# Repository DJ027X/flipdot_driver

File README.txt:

######################
A word about the license
######################
In this repo, you'll find the EDA design files for my RISC-V based flipdot display driver.
In the interest of preventing an entity from profiting off of my work or its derivitives without my permission, everything in this repo is released under the Creative Commons license BY-NC-SA.
Feel free to modify and redistribute my work (with attribution to me, and under the same BY-NC-SA license), just don't use the work for profit.
Please contact me if you would like to request exemption from the terms of the license.

######################
Project progress
######################
This project is INCOMPLETE and IN-PROGRESS.
At the moment, only the schematic exists; no layout design yet.
The schematic is very near completion, and I'm currently working on finishing touches, and reviewing the design.

######################
Design details/notes
######################
This project is being designed with the open-source KiCAD toolchain. I'm tending toward openness with this project, but my design does use an FT2232D, and my license isn't truly FOSS compliant. More FOSS friendly versions may come up in the future.
My flipdot display driver is intended for use with a Luminator MAX 3000 flipdot display.
My board will mount onto the back of the flipdot display, and connect to it via a board-to-board connector (samtec part SSQ-132-01-G-Q at the moment).
Each dot on the Luminator MAX 3000 is matrixed in such a way that lends itself to be driven by what is essentially an H-bridge. (diodes in the display circuitry complicate things a tad, which is why it's not exactly an H-bridge driver, but pretty close)
My driver uses power MOSFETs arranged in an H-bridge-like topology to drive current in short (on the order of millisecond) pulses in one direction or another through the coil of each dot to flip it on (bright side visable) or off (black side visible), depending on the cirection of the current
There is 1/2 of this H-bridge-like circuit (quarter bridge?) driving each row and column on the display, effectively allowing the driver to multiplex the dots.
The quarter-bridge driver circuitry is controlled by data stored in 2 (extendable) shift registers, one for the rows and one for the columns.
Pulsing an output enable signal on the shift registers drives the selected quarter-bridge circuits (based on the output from the shift register) for the duration of the pulse.
If one wishes to extend their display with yet another (actually, an arbitrary number of) Luminator MAX 3000 board, I've added a connector that will be used (when I get around to designing the second board) to extend the shift registers to the additional board, which will house it's own section of the shift register and dedicated quarter-bridge driver circuitry.
The brain of the operation is the FE310-G000, a VERY new RISC-V based microcontroller released by SiFive.
Along with the uC are the typical auxilary chips: memory and serial to UART/JTAG to program the uC.
The Luminator MAX 3000 also has 1 LED per dot. They are all connected to the same power pins, so they're either all on, or all off.
I intend to control the brightness with PWM.
Under normal use, the board will be supplied with 12V from a power brick. From there, several buck converters will provide the voltages for the shift registers, memory, uC, etc.
There will also be a voltage negater (generating -12V), to provide a potential of 24V for the LEDs.
I'm currently working full time, so progress on this relatively large hobby project has been slow, but I'll have a physical board eventually! (Aiming for 3 months from now (12/27/2018))

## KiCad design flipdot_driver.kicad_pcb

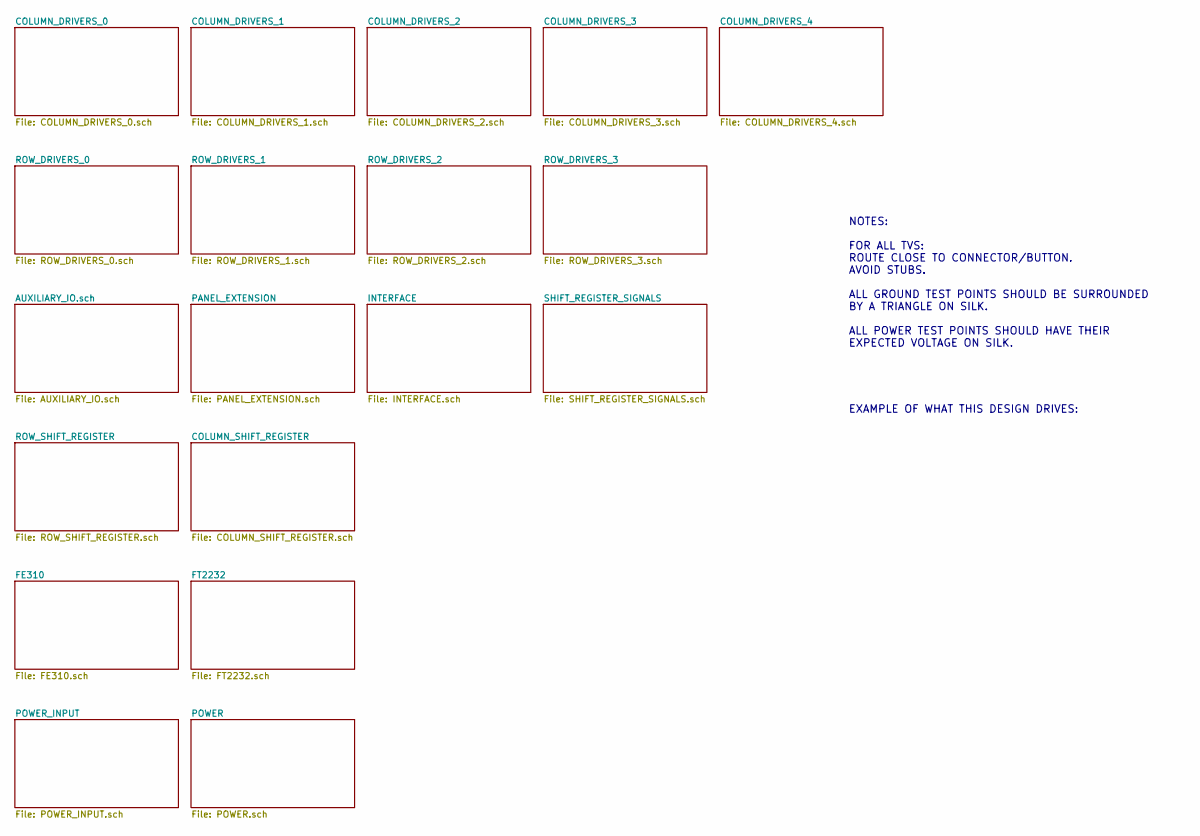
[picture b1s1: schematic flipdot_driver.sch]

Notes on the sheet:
NOTES: FOR ALL TVS: ROUTE CLOSE TO CONNECTOR/BUTTON. AVOID STUBS. ALL GROUND TEST POINTS SHOULD BE SURROUNDED BY A TRIANGLE ON SILK. ALL POWER TEST POINTS SHOULD HAVE THEIR EXPECTED VOLTAGE ON SILK.
EXAMPLE OF WHAT THIS DESIGN DRIVES:

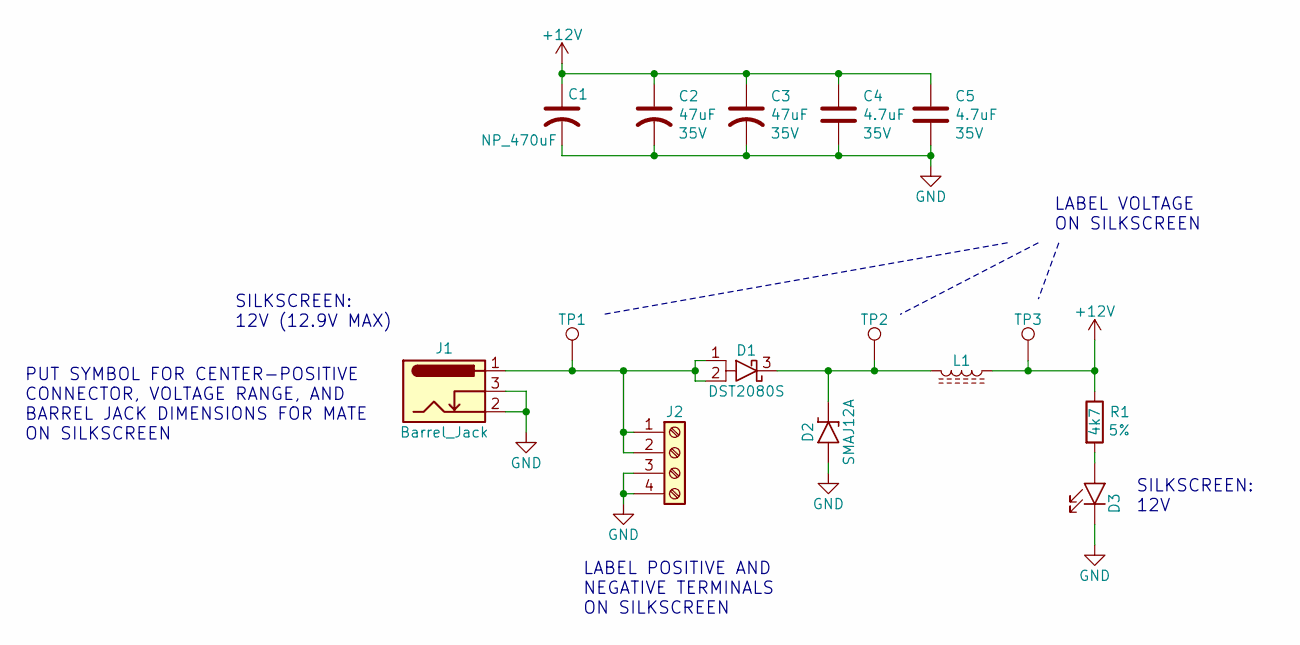
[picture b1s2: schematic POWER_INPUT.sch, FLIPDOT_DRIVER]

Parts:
C1: NP_470uF
C2, C3: ‎ESK476M035AC3AA‎; Rating 35V
C4, C5: ‎CL21A475KLCLQNC‎; C_0805_2012Metric; Rating 35V
D1: DST2080S; TO-277B
D2: SMAJ12A; D_SMA
D3: LED_GENERIC_0805; D_0805_2012Metric
J1: Barrel_Jack; BarrelJack_Wuerth_6941xx301002
J2: Screw_Terminal_01x04; TERMINAL_BLOCK_5mm_1x4
L1: BLM31SN500SZ1L; L_1206_3216Metric
R1: CRG0603F4K7; R_0603_1608Metric; TOLERANCE 5%
TP1, TP2, TP3: TestPoint; TestPoint_THTPad_D1.0mm_Drill0.5mm

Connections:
+12V: C1.1, C2.1, C3.1, C4.1, C5.1, L1.1, R1.1, TP3.1; also elsewhere on the board
GND: C1.2, C2.2, C3.2, C4.2, C5.2, D2.2 (A), D3.1 (K), J1.2, J1.3, J2.3, J2.4; also elsewhere on the board
unnamed: D1.1 (A1), D1.2 (A2), J1.1, J2.1, J2.2, TP1.1
unnamed: D1.3 (K), D2.1 (K), L1.2, TP2.1
unnamed: D3.2 (A), R1.2

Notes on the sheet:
PUT SYMBOL FOR CENTER-POSITIVE CONNECTOR, VOLTAGE RANGE, AND BARREL JACK DIMENSIONS FOR MATE ON SILKSCREEN
LABEL POSITIVE AND NEGATIVE TERMINALS ON SILKSCREEN
SILKSCREEN: 12V (12.9V MAX)
SILKSCREEN: 12V
LABEL VOLTAGE ON SILKSCREEN

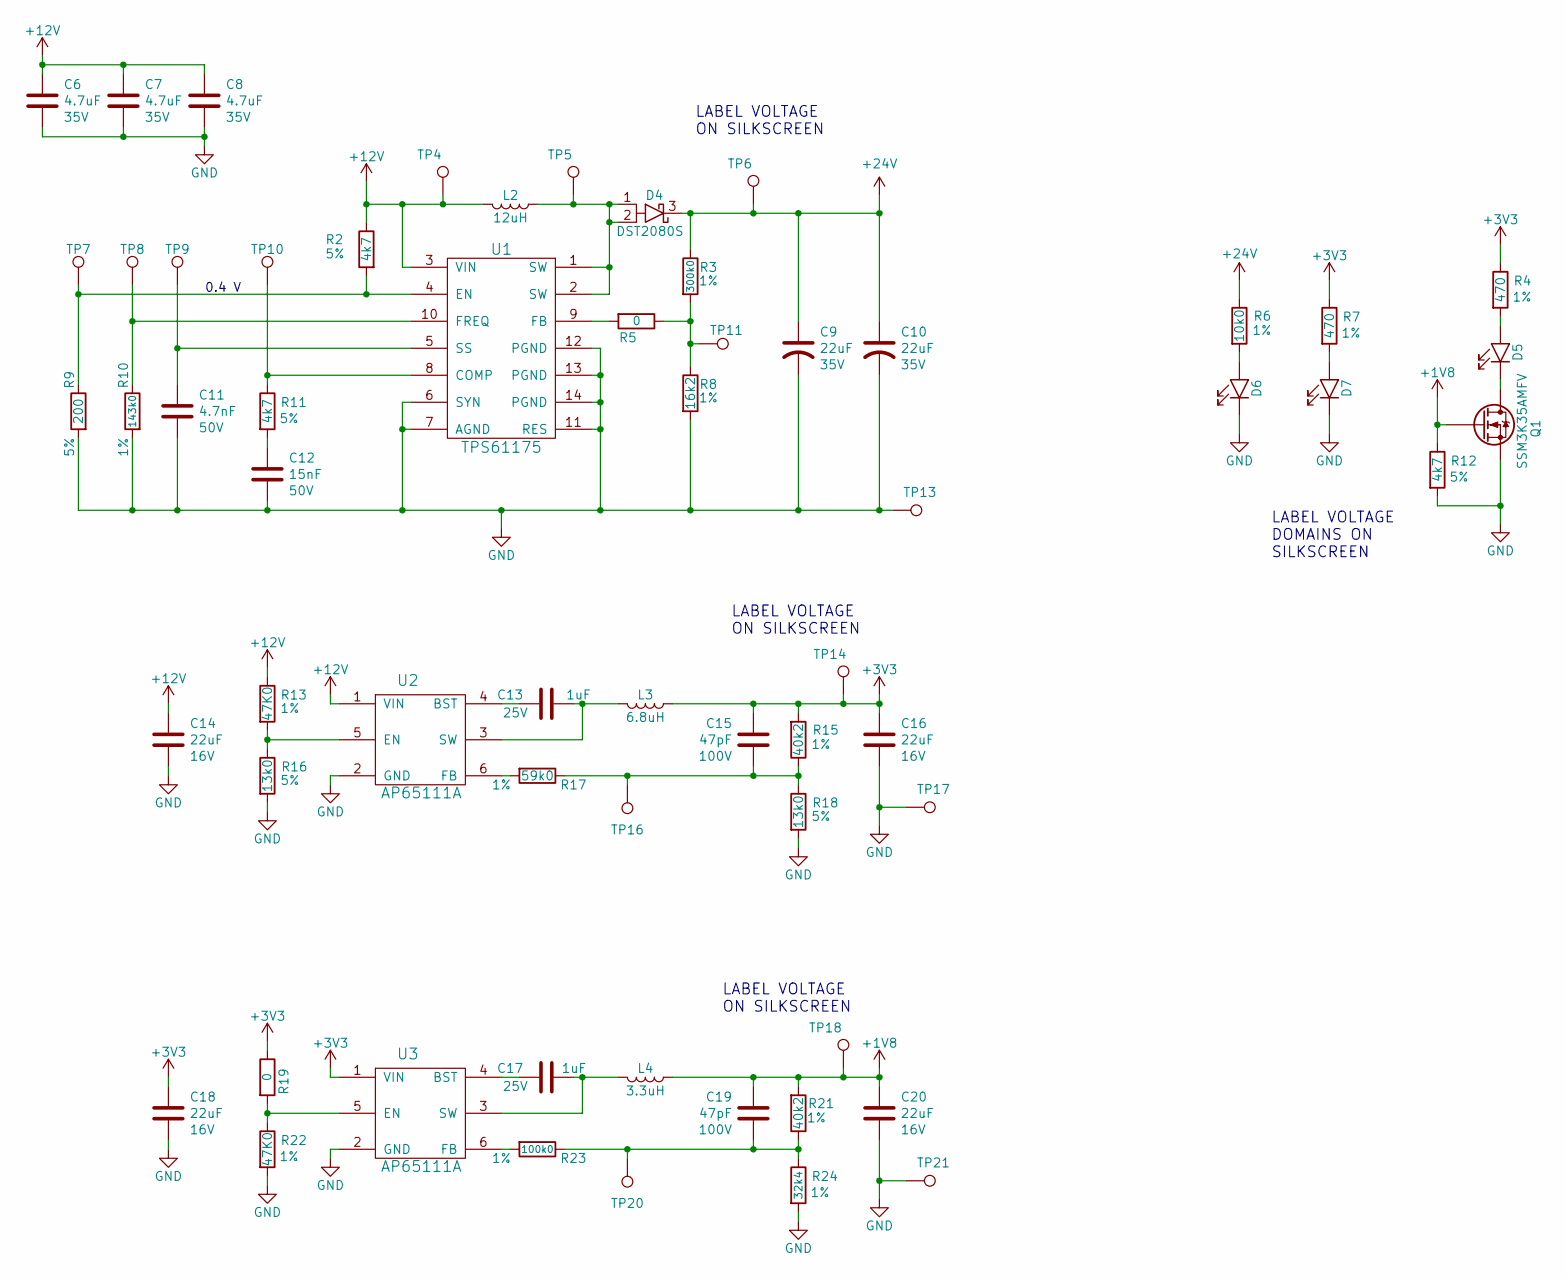
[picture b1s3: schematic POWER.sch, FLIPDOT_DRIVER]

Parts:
C6, C7, C8: ‎CL21A475KLCLQNC‎; C_0805_2012Metric; Rating 35V
C9, C10: EEE-1VA220SP; Rating 35V
C11: 885012206087; C_0603_1608Metric; Rating 50V
C12: ‎CL10B153KB8SFNC‎; C_0603_1608Metric; Rating 50V
C13, C17: CL10B105KA8NNNC; C_0603_1608Metric; Rating 25V
C14, C16, C18, C20: CL21A226MOCLRNC; C_0805_2012Metric; Rating 16V
C15, C19: ‎C0603C470J1GACTU‎; C_0603_1608Metric; Rating 100V
D4: DST2080S; TO-277B
D5, D6, D7: LED_GENERIC_0805; D_0805_2012Metric
L2: #B966AS-120M=P3; 490-14124-1-ND
L3: NRS5020T6R8MMGJ
L4: MAKK2016T3R3M
Q1: SSM3K35AMFV; SOT-723
R2, R11, R12: CRG0603F4K7; R_0603_1608Metric; TOLERANCE 5%
R3: CR0603-FX-3003ELF; R_0603; TOLERANCE 1%
R4, R7: ‎RMCF0603FT470R‎; R_0603_1608Metric; TOLERANCE 1%
R5, R19: RC0603JR-070RL; R_0603_1608Metric
R6: RMCF0603FT10K0; R_0603; TOLERANCE 1%
R8: RMCF0603FT16K2; R_0603; TOLERANCE 1%
R9: AC0603JR-07200RL; R_0603; TOLERANCE 5%
R10: ERJ-3EKF1433V; R_0603; TOLERANCE 1%
R13, R22: RC0603FR-0747KL; R_0603_1608Metric; TOLERANCE 1%
R15, R21: RMCF0603FT40K2; R_0603; TOLERANCE 1%
R16, R18: RMCF0603JT13K0; R_0603; TOLERANCE 5%
R17: RMCF0603FT59K0; R_0603; TOLERANCE 1%
R23: RMCF0603FG100K; R_0603; TOLERANCE 1%
R24: CR0603-FX-3242ELF; R_0603_1608Metric; TOLERANCE 1%
TP4, TP5, TP6, TP7, TP8, TP9, TP10, TP11, TP13, TP14, TP16, TP17, TP18, TP20, TP21: TestPoint; TestPoint_THTPad_D1.0mm_Drill0.5mm
U1: TPS61175; HTSSOP-14
U2, U3: AP65111A; TSOT-23-6

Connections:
+1V8: C19.1, C20.1, L4.1, Q1.1 (G), R12.1, R21.1, TP18.1; also elsewhere on the board
+3V3: C15.1, C16.1, C18.1, L3.1, R4.1, R7.1, R15.1, R19.1, TP14.1, U3.1 (VIN); also elsewhere on the board
+12V: C6.1, C7.1, C8.1, C14.1, L2.2, R2.1, R13.1, TP4.1, U1.3 (VIN), U2.1 (VIN); also elsewhere on the board
+24V: C9.1, C10.1, D4.3 (K), R3.1, R6.1, TP6.1; also elsewhere on the board
GND: C6.2, C7.2, C8.2, C9.2, C10.2, C11.2, C12.2, C14.2, C16.2, C18.2, C20.2, D6.1 (K), D7.1 (K), Q1.2 (S), R8.2, R9.2, R10.2, R12.2, R16.2, R18.2, R22.2, R24.2, TP13.1, TP17.1, TP21.1, U1.6 (SYN), U1.7 (AGND), U1.11 (RES), U1.12 (PGND), U1.13 (PGND), U1.14 (PGND), U1.15 (Thermal_Pad), U2.2 (GND), U3.2 (GND); also elsewhere on the board
unnamed: C11.1, TP9.1, U1.5 (SS)
unnamed: C12.1, R11.2
unnamed: C13.1, U2.4 (BST)
unnamed: C13.2, L3.2, U2.3 (SW)
unnamed: C15.2, R15.2, R17.1, R18.1, TP16.1
unnamed: C17.1, U3.4 (BST)
unnamed: C17.2, L4.2, U3.3 (SW)
unnamed: C19.2, R21.2, R23.1, R24.1, TP20.1
unnamed: D4.1 (A1), D4.2 (A2), L2.1, TP5.1, U1.1 (SW), U1.2 (SW)
unnamed: D5.1 (K), Q1.3 (D)
unnamed: D5.2 (A), R4.2
unnamed: D6.2 (A), R6.2
unnamed: D7.2 (A), R7.2
unnamed: R2.2, R9.1, TP7.1, U1.4 (EN)
unnamed: R3.2, R5.1, R8.1, TP11.1
unnamed: R5.2, U1.9 (FB)
unnamed: R10.1, TP8.1, U1.10 (FREQ)
unnamed: R11.1, TP10.1, U1.8 (COMP)
unnamed: R13.2, R16.1, U2.5 (EN)
unnamed: R17.2, U2.6 (FB)
unnamed: R19.2, R22.1, U3.5 (EN)
unnamed: R23.2, U3.6 (FB)

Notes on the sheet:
0.4 V
LABEL VOLTAGE DOMAINS ON SILKSCREEN
LABEL VOLTAGE ON SILKSCREEN

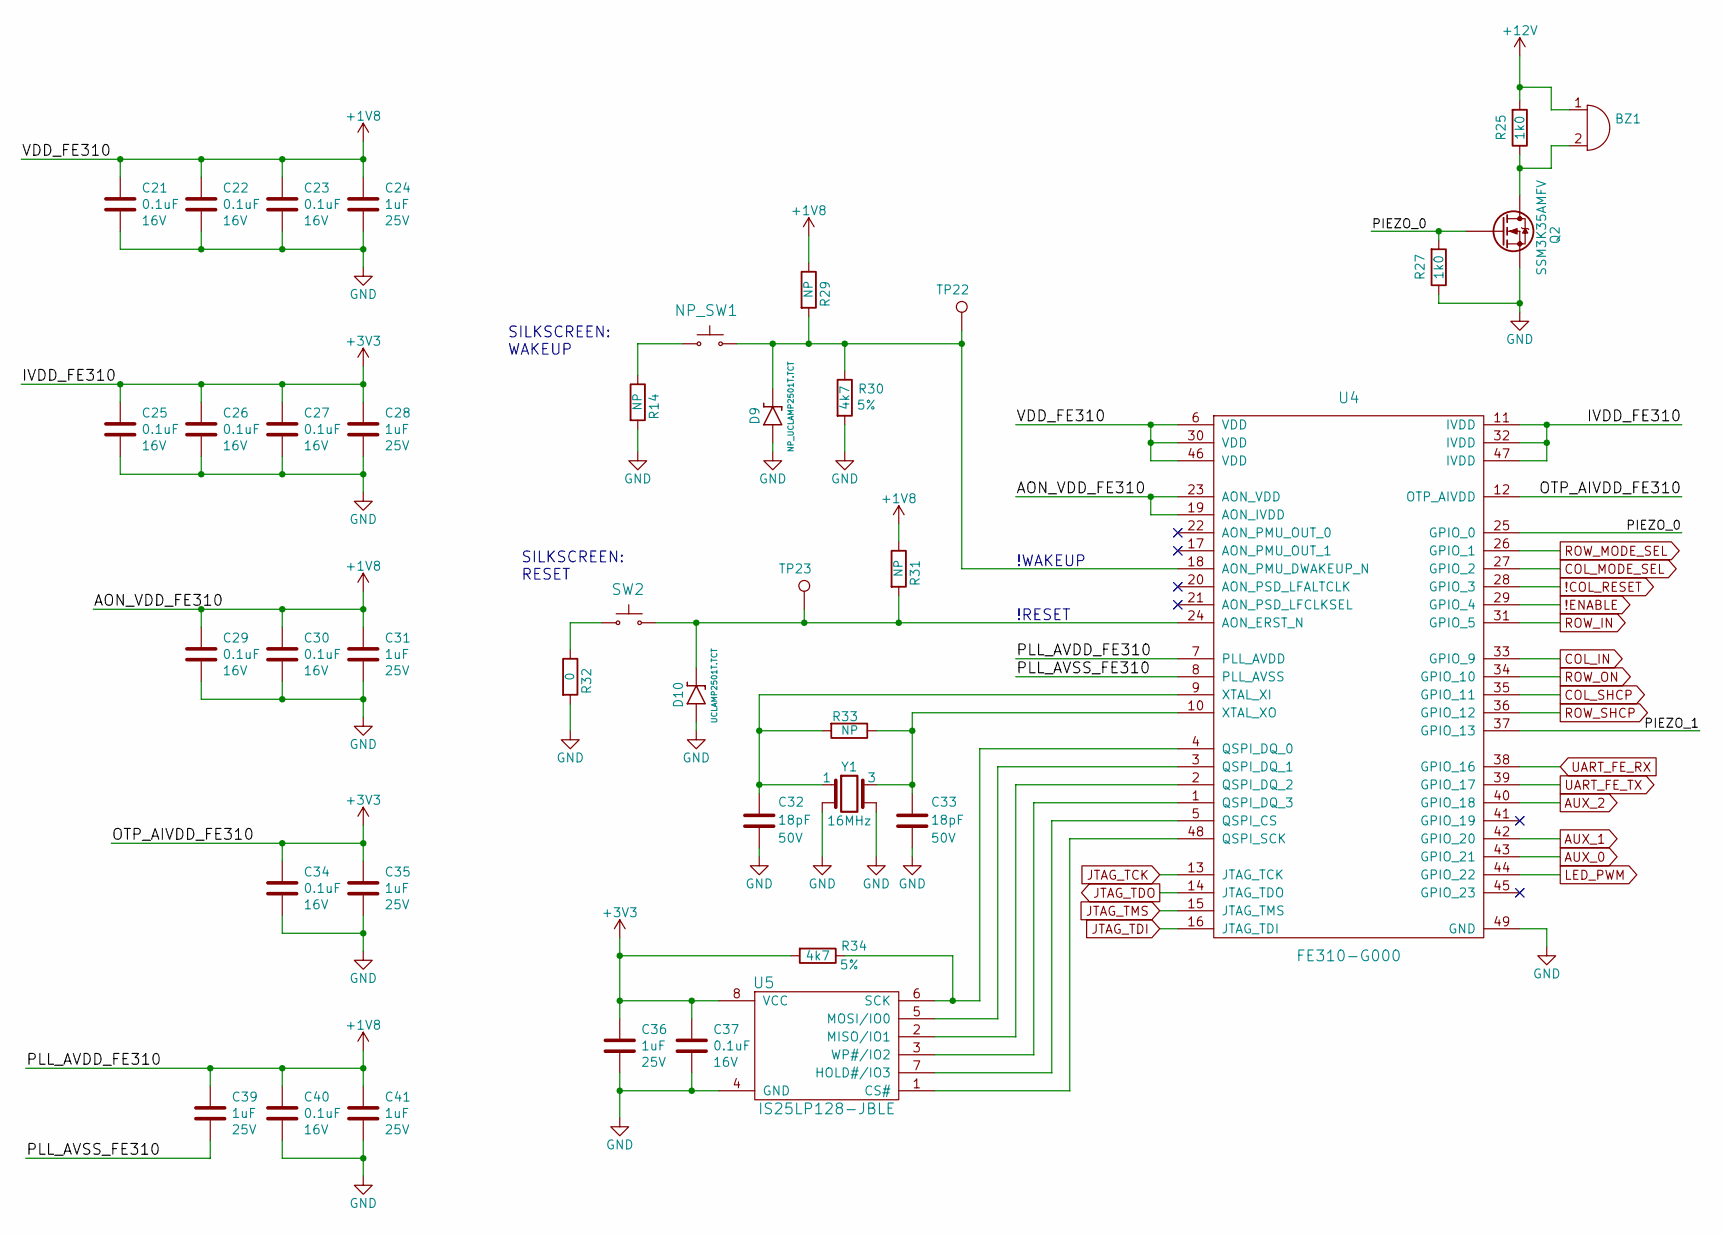
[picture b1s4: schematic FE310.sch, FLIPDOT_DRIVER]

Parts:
BZ1: PASSIVE_BUZZER; 0.5_IN_BUZZER
C21, C22, C23, C25, C26, C27, C29, C30, C34, C37, C40: CL10B104KO8NNNC; C_0603_1608Metric; Rating 16V
C24, C28, C31, C35, C36, C39, C41: CL10B105KA8NNNC; C_0603_1608Metric; Rating 25V
C32, C33: C0603C180K5RACAUTO; C_0603_1608Metric; Rating 50V
D9: NP_UCLAMP2501T.TCT; SLP1006P2T
D10: UCLAMP2501T.TCT; SLP1006P2T
NP_SW1: NP_TACTILE_SWITCH_SMALL; TACTILE_SWITCH_SMALL
Q2: SSM3K35AMFV; SOT-723
R14, R29, R31, R33: NP_R_0603; R_0603_1608Metric
R25, R27: RC0603JR-071KL; R_0603_1608Metric
R30, R34: CRG0603F4K7; R_0603_1608Metric; TOLERANCE 5%
R32: RC0603JR-070RL; R_0603_1608Metric
SW2: TACTILE_SWITCH_SMALL
TP22, TP23: TestPoint; TestPoint_THTPad_D1.0mm_Drill0.5mm
U4: FE310-G000; QFN-48-1EP_6x6mm_P0.4mm_EP4.3x4.3mm
U5: IS25LP128-JBLE; SOIC-8_3.9x4.9mm_P1.27mm
Y1: 16MHz; 7M-16.000MAAE-T

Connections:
!COL_RESET: U4.28 (GPIO_3); also elsewhere on the board
!ENABLE: U4.29 (GPIO_4); also elsewhere on the board
+1V8: C21.1, C22.1, C23.1, C24.1, C29.1, C30.1, C31.1, C39.1, C40.1, C41.1, R29.1, R31.1, U4.6 (VDD), U4.7 (PLL_AVDD), U4.19 (AON_IVDD), U4.23 (AON_VDD), U4.30 (VDD), U4.46 (VDD); also elsewhere on the board
+3V3: C25.1, C26.1, C27.1, C28.1, C34.1, C35.1, C36.1, C37.1, R34.2, U4.11 (IVDD), U4.12 (OTP_AIVDD), U4.32 (IVDD), U4.47 (IVDD), U5.8 (VCC); also elsewhere on the board
+12V: BZ1.1 (-), R25.1; also elsewhere on the board
/FE310/PIEZO_0: Q2.1 (G), R27.1, U4.25 (GPIO_0)
/FE310/PIEZO_1: U4.37 (GPIO_13)
/FE310/PLL_AVSS_FE310: C39.2, U4.8 (PLL_AVSS)
COL_IN: U4.33 (GPIO_9); also elsewhere on the board
COL_MODE_SEL: U4.27 (GPIO_2); also elsewhere on the board
COL_SHCP: U4.35 (GPIO_11); also elsewhere on the board
GND: C21.2, C22.2, C23.2, C24.2, C25.2, C26.2, C27.2, C28.2, C29.2, C30.2, C31.2, C32.2, C33.2, C34.2, C35.2, C36.2, C37.2, C40.2, C41.2, D9.2 (A), D10.2 (A), Q2.2 (S), R14.2, R27.2, R30.2, R32.2, U4.49 (GND), U5.4 (GND), Y1.2, Y1.4; also elsewhere on the board
JTAG_TCK: U4.13 (JTAG_TCK); also elsewhere on the board
JTAG_TDI: U4.16 (JTAG_TDI); also elsewhere on the board
JTAG_TDO: U4.14 (JTAG_TDO); also elsewhere on the board
JTAG_TMS: U4.15 (JTAG_TMS); also elsewhere on the board
LED_PWM: U4.44 (GPIO_22); also elsewhere on the board
unnamed: BZ1.2 (+), Q2.3 (D), R25.2
unnamed: C32.1, R33.2, U4.9 (XTAL_XI), Y1.1
unnamed: C33.1, R33.1, U4.10 (XTAL_XO), Y1.3
unnamed: D9.1 (K), NP_SW1.2, R29.2, R30.1, TP22.1, U4.18 (AON_PMU_DWAKEUP_N)
unnamed: D10.1 (K), R31.2, SW2.2, TP23.1, U4.24 (AON_ERST_N)
unnamed: NP_SW1.1, R14.1
unnamed: R32.1, SW2.1
unnamed: R34.1, U4.4 (QSPI_DQ_0), U5.6 (SCK)
unnamed: U4.1 (QSPI_DQ_3), U5.3 (WP#/IO2)
unnamed: U4.2 (QSPI_DQ_2), U5.2 (MISO/IO1)
unnamed: U4.3 (QSPI_DQ_1), U5.5 (MOSI/IO0)
unnamed: U4.5 (QSPI_CS), U5.7 (HOLD#/IO3)
unnamed: U4.48 (QSPI_SCK), U5.1 (CS#)
ROW_IN: U4.31 (GPIO_5); also elsewhere on the board
ROW_MODE_SEL: U4.26 (GPIO_1); also elsewhere on the board
ROW_ON: U4.34 (GPIO_10); also elsewhere on the board
ROW_SHCP: U4.36 (GPIO_12); also elsewhere on the board
UART_FE_RX: U4.38 (GPIO_16); also elsewhere on the board
UART_FE_TX: U4.39 (GPIO_17); also elsewhere on the board

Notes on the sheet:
SILKSCREEN: RESET
SILKSCREEN: WAKEUP
!WAKEUP
!RESET

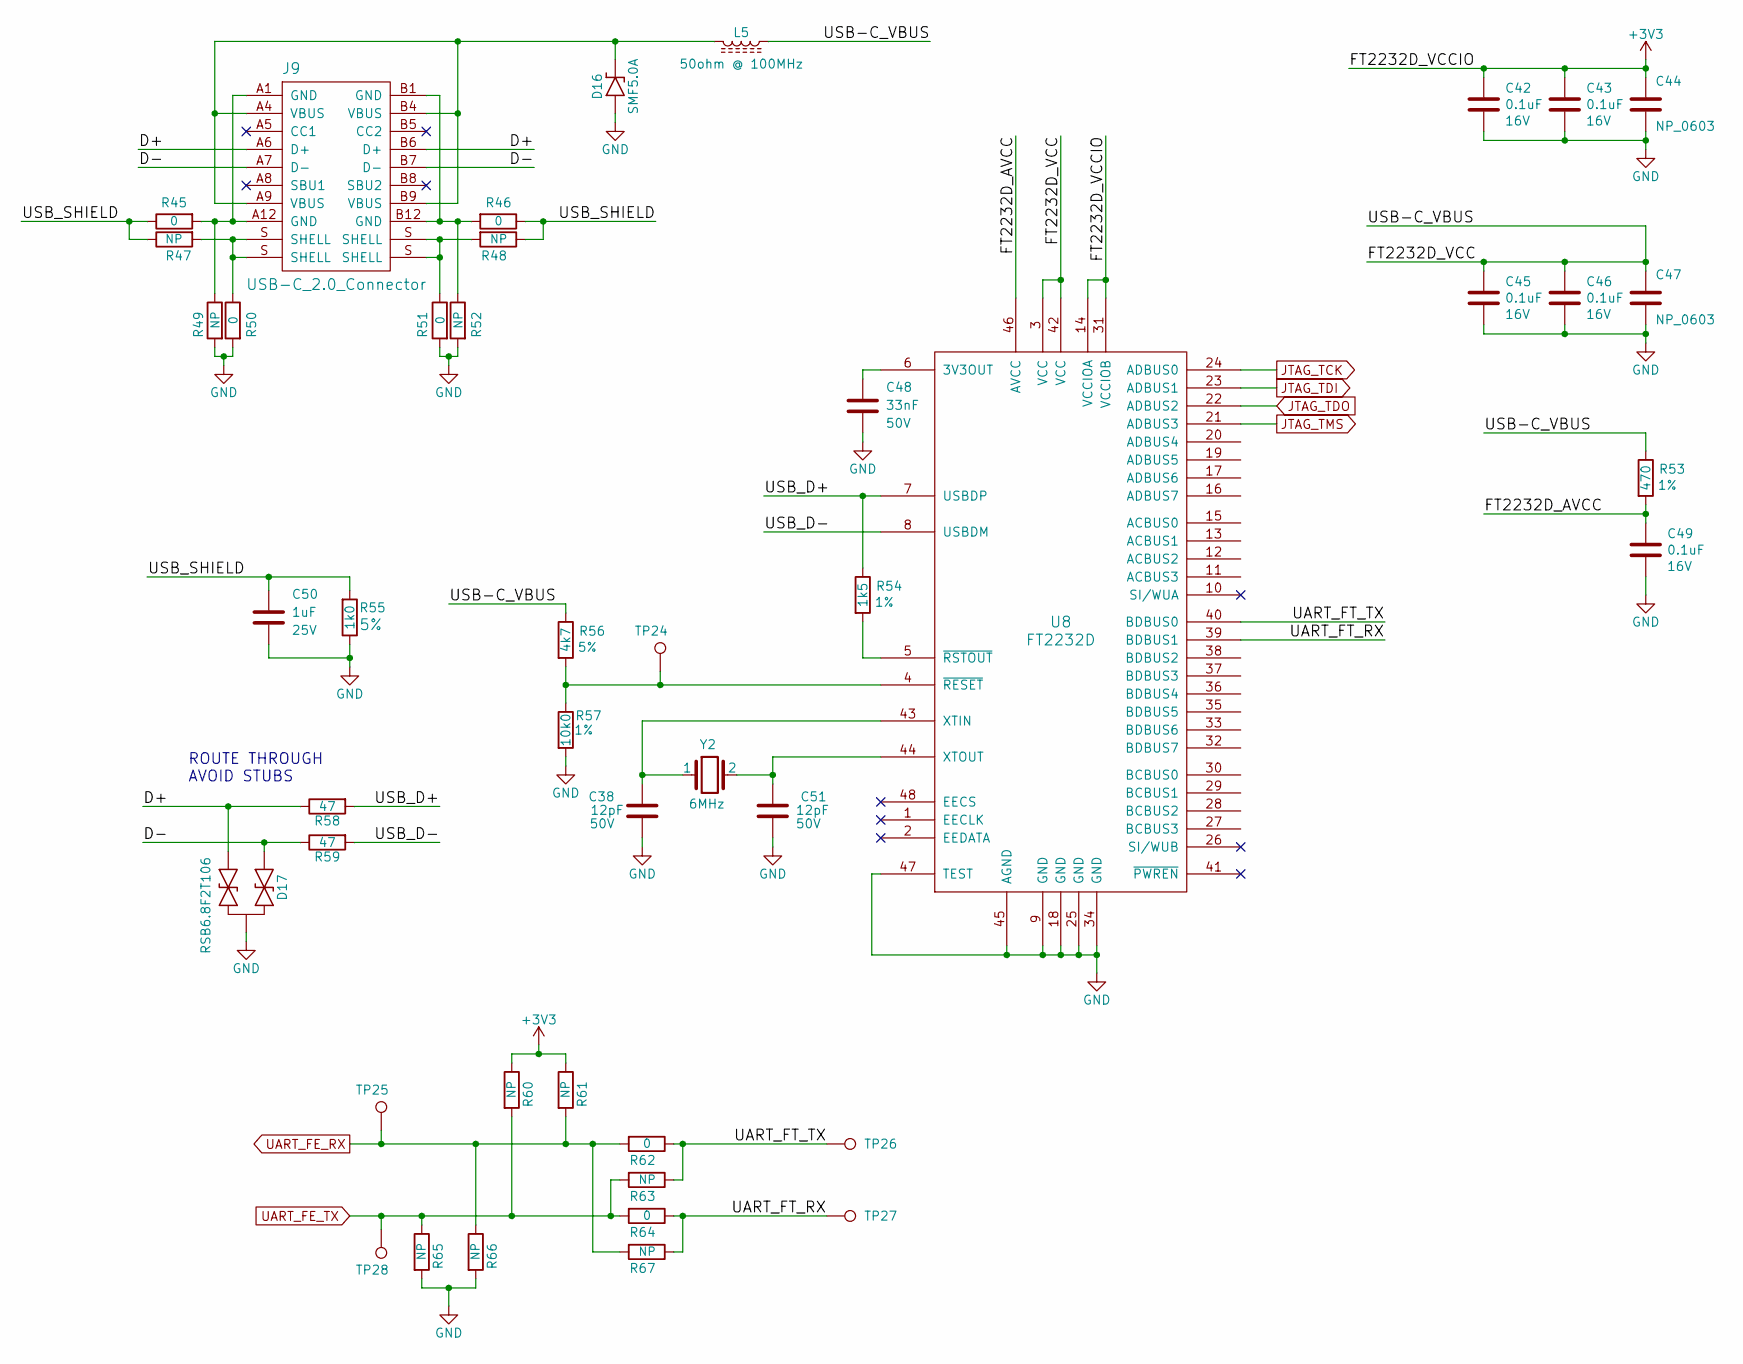
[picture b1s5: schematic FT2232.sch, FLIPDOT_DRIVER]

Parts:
C38, C51: GRM1555C1H120JA01D; C_0402_1005Metric; RATING 50V; TOLERANCE 5%
C42, C43, C45, C46, C49: CL10B104KO8NNNC; C_0603_1608Metric; Rating 16V
C44, C47: NP_C_0603; C_0603_1608Metric
C48: CL10B333KB8SFNC; C_0603_1608Metric; Rating 50V
C50: CL10B105KA8NNNC; C_0603_1608Metric; Rating 25V
D16: SMF5.0A; SOD-123FL
D17: RSB6.8F2T106; SOT-323_SC-70
J9: USB-C_2.0_Connector; USB4085-GF-A
L5: BLM31SN500SZ1L; L_1206_3216Metric
R45, R46, R50, R51, R62, R64: RC0603JR-070RL; R_0603_1608Metric
R47, R48, R49, R52, R60, R61, R63, R65, R66, R67: NP_R_0603; R_0603_1608Metric
R53: ‎RMCF0603FT470R‎; R_0603_1608Metric; TOLERANCE 1%
R54: RMCF0603FT1K50; R_0603_1608Metric; TOLERANCE 1%
R55: RC0603JR-071KL; R_0603_1608Metric; TOLERANCE 5%
R56: CRG0603F4K7; R_0603_1608Metric; TOLERANCE 5%
R57: RMCF0603FT10K0; R_0603; TOLERANCE 1%
R58, R59: 47; R_0603_1608Metric
TP24, TP25, TP26, TP27, TP28: TestPoint; TestPoint_THTPad_D1.0mm_Drill0.5mm
U8: FT2232D; LQFP-48_7x7mm_P0.5mm
Y2: NX8045GB-6MHZ-STD-CSF-3; NX8045GB

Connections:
+3V3: C42.1, C43.1, C44.1, R60.1, R61.1, U8.14 (VCCIOA), U8.31 (VCCIOB); also elsewhere on the board
/FT2232/D+: D17.1, J9.A6 (D+), J9.B6 (D+), R58.1
/FT2232/D-: D17.2, J9.A7 (D-), J9.B7 (D-), R59.1
/FT2232/FT2232D_AVCC: C49.1, R53.2, U8.46 (AVCC)
/FT2232/FT2232D_VCC: C45.1, C46.1, C47.1, L5.1, R53.1, R56.1, U8.3 (VCC), U8.42 (VCC)
/FT2232/UART_FT_RX: R64.1, R67.1, TP27.1, U8.39 (BDBUS1)
/FT2232/UART_FT_TX: R62.1, R63.1, TP26.1, U8.40 (BDBUS0)
/FT2232/USB_D+: R54.1, R58.2, U8.7 (USBDP)
/FT2232/USB_D-: R59.2, U8.8 (USBDM)
/FT2232/USB_SHIELD: C50.1, R45.1, R46.1, R47.1, R48.1, R55.1
GND: C38.2, C42.2, C43.2, C44.2, C45.2, C46.2, C47.2, C48.2, C49.2, C50.2, C51.2, D16.2 (A), D17.3, R49.2, R50.2, R51.2, R52.2, R55.2, R57.2, R65.2, R66.2, U8.9 (GND), U8.18 (GND), U8.25 (GND), U8.34 (GND), U8.45 (AGND), U8.47 (TEST); also elsewhere on the board
JTAG_TCK: U8.24 (ADBUS0); also elsewhere on the board
JTAG_TDI: U8.23 (ADBUS1); also elsewhere on the board
JTAG_TDO: U8.22 (ADBUS2); also elsewhere on the board
JTAG_TMS: U8.21 (ADBUS3); also elsewhere on the board
unnamed: C38.1, U8.43 (XTIN), Y2.1
unnamed: C48.1, U8.6 (3V3OUT)
unnamed: C51.1, U8.44 (XTOUT), Y2.2
unnamed: D16.1 (K), J9.A4 (VBUS), J9.A9 (VBUS), J9.B4 (VBUS), J9.B9 (VBUS), L5.2
unnamed: J9.A1 (GND), J9.A12 (GND), R45.2, R49.1
unnamed: J9.B1 (GND), J9.B12 (GND), R46.2, R52.1
unnamed: R54.2, U8.5 (~RSTOUT)
unnamed: R56.2, R57.1, TP24.1, U8.4 (~RESET)
UART_FE_RX: R61.2, R62.2, R66.1, R67.2, TP25.1; also elsewhere on the board
UART_FE_TX: R60.2, R63.2, R64.2, R65.1, TP28.1; also elsewhere on the board

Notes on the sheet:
ROUTE THROUGH AVOID STUBS

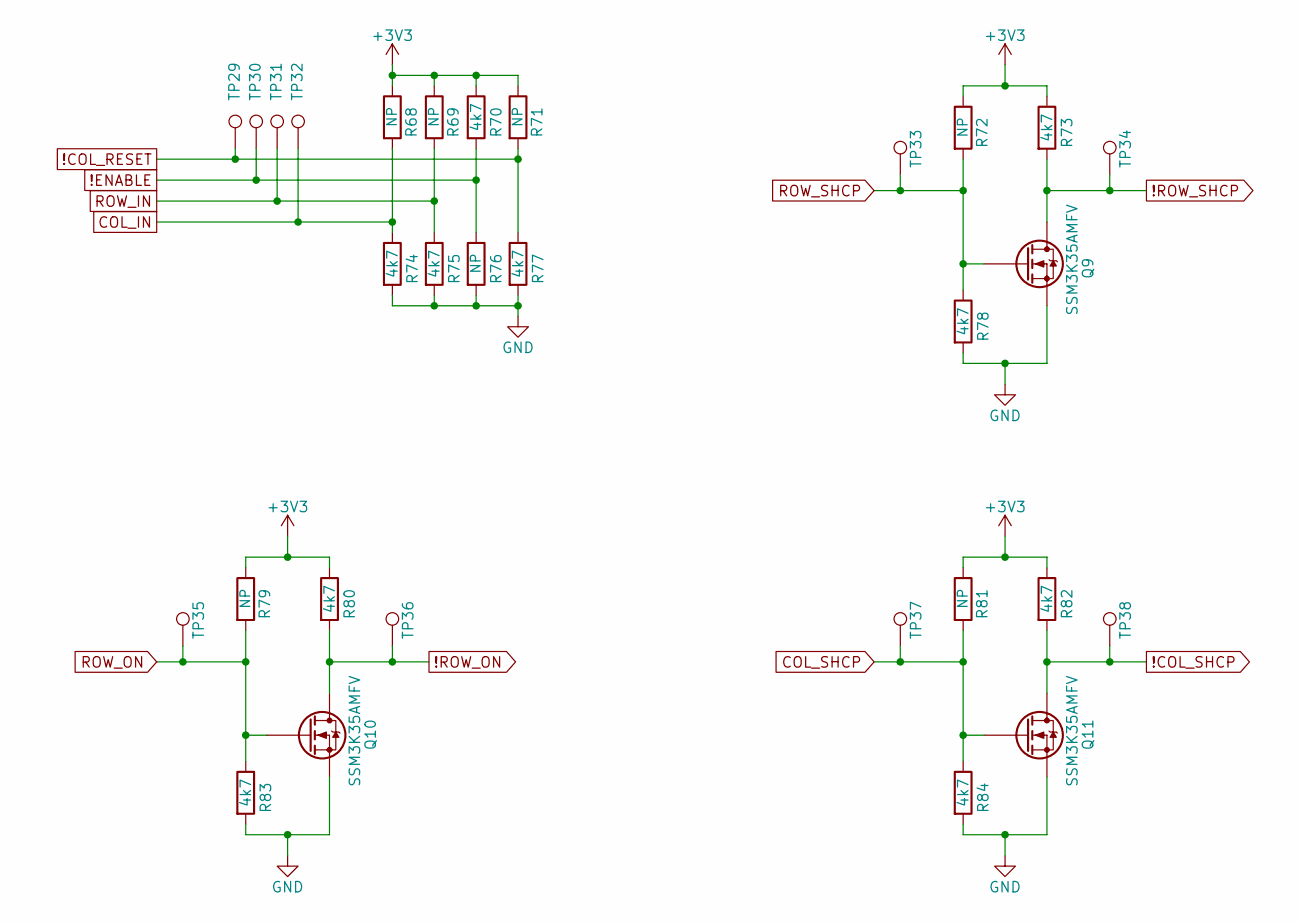
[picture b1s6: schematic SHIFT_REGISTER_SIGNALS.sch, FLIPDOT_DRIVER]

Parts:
Q9, Q10, Q11: SSM3K35AMFV; SOT-723
R68, R69, R71, R72, R76, R79, R81: NP_R_0603; R_0603_1608Metric
R70, R73, R74, R75, R77, R78, R80, R82, R83, R84: CRG0603F4K7; R_0603_1608Metric; TOLERANCE 5%
TP29, TP30, TP31, TP32, TP33, TP34, TP35, TP36, TP37, TP38: TestPoint; TestPoint_THTPad_D1.0mm_Drill0.5mm

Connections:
!COL_RESET: R71.2, R77.1, TP29.1; also elsewhere on the board
!COL_SHCP: Q11.3 (D), R82.2, TP38.1; also elsewhere on the board
!ENABLE: R70.2, R76.1, TP30.1; also elsewhere on the board
!ROW_ON: Q10.3 (D), R80.2, TP36.1; also elsewhere on the board
!ROW_SHCP: Q9.3 (D), R73.2, TP34.1; also elsewhere on the board
+3V3: R68.1, R69.1, R70.1, R71.1, R72.1, R73.1, R79.1, R80.1, R81.1, R82.1; also elsewhere on the board
COL_IN: R68.2, R74.1, TP32.1; also elsewhere on the board
COL_SHCP: Q11.1 (G), R81.2, R84.1, TP37.1; also elsewhere on the board
GND: Q9.2 (S), Q10.2 (S), Q11.2 (S), R74.2, R75.2, R76.2, R77.2, R78.2, R83.2, R84.2; also elsewhere on the board
ROW_IN: R69.2, R75.1, TP31.1; also elsewhere on the board
ROW_ON: Q10.1 (G), R79.2, R83.1, TP35.1; also elsewhere on the board
ROW_SHCP: Q9.1 (G), R72.2, R78.1, TP33.1; also elsewhere on the board

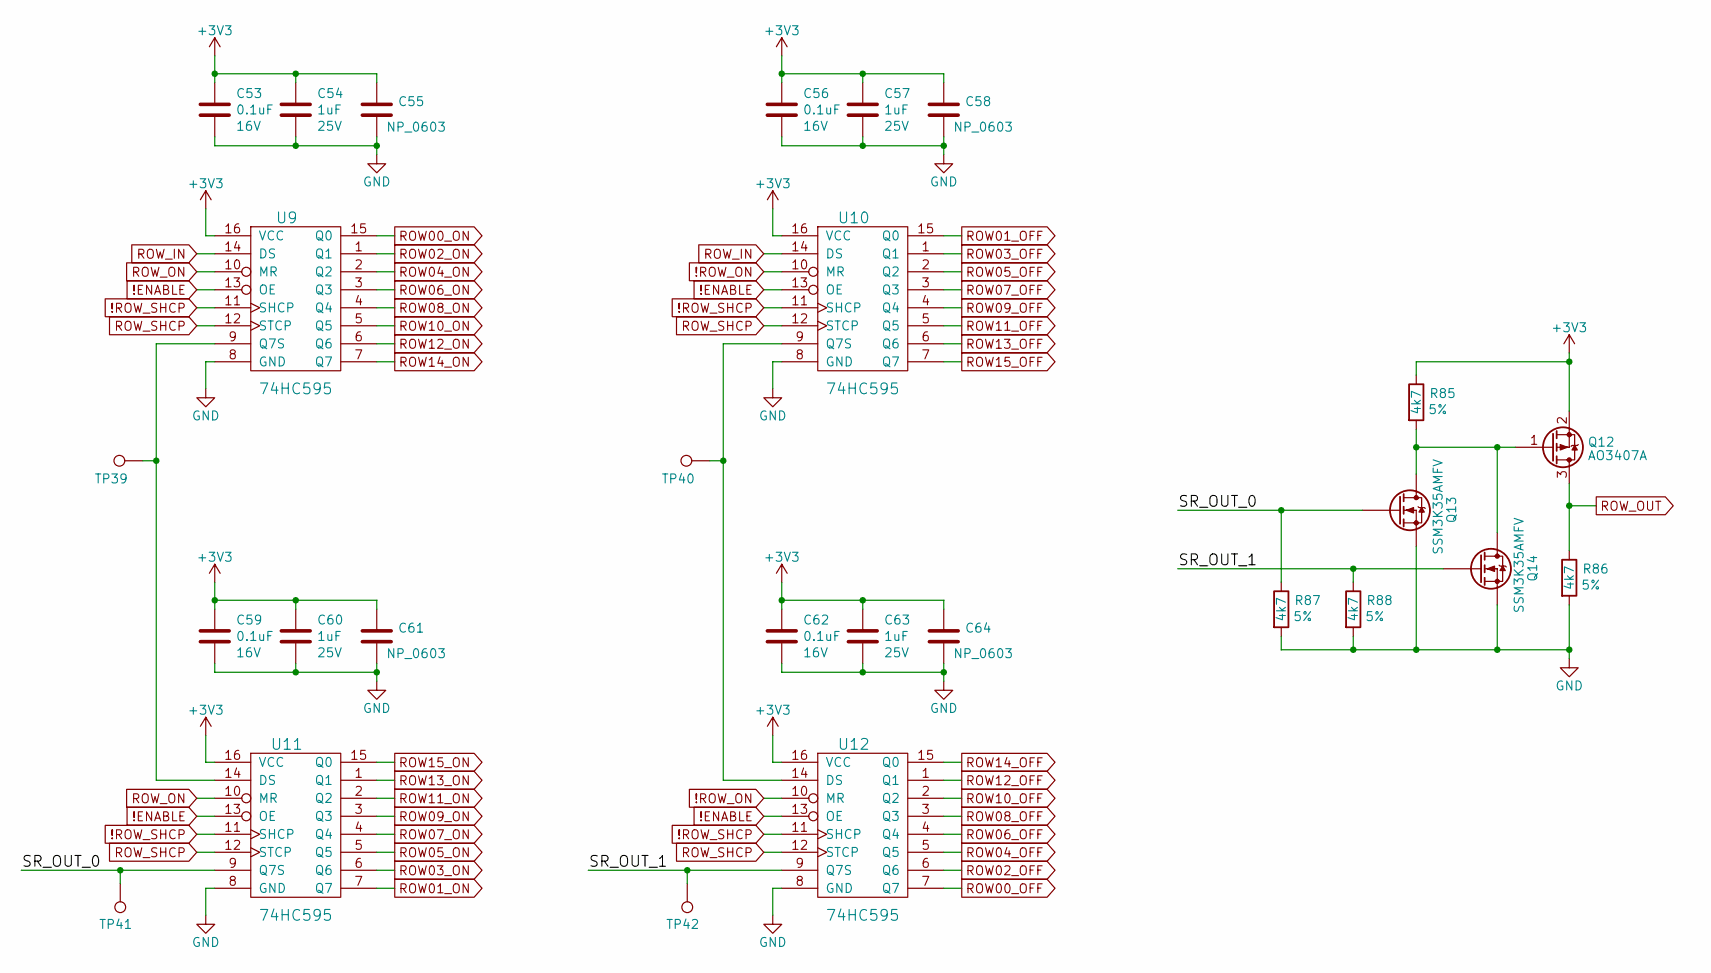
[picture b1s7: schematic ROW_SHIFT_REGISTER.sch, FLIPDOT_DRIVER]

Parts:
C53, C56, C59, C62: CL10B104KO8NNNC; C_0603_1608Metric; Rating 16V
C54, C57, C60, C63: CL10B105KA8NNNC; C_0603_1608Metric; Rating 25V
C55, C58, C61, C64: NP_0603; C_0603_1608Metric
Q12: AO3407A; SOT-23
Q13, Q14: SSM3K35AMFV; SOT-723
R85, R86, R87, R88: CRG0603F4K7; R_0603_1608Metric; TOLERANCE 5%
TP39, TP40, TP41, TP42: TestPoint; TestPoint_THTPad_D1.0mm_Drill0.5mm
U9, U10, U11, U12: 74HC595; SOIC-16_3.9x9.9mm_P1.27mm

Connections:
!ENABLE: U9.13 (OE), U10.13 (OE), U11.13 (OE), U12.13 (OE); also elsewhere on the board
!ROW_ON: U10.10 (MR), U12.10 (MR); also elsewhere on the board
!ROW_SHCP: U9.11 (SHCP), U10.11 (SHCP), U11.11 (SHCP), U12.11 (SHCP); also elsewhere on the board
+3V3: C53.1, C54.1, C55.1, C56.1, C57.1, C58.1, C59.1, C60.1, C61.1, C62.1, C63.1, C64.1, Q12.2 (S), R85.1, U9.16 (VCC), U10.16 (VCC), U11.16 (VCC), U12.16 (VCC); also elsewhere on the board
/ROW_SHIFT_REGISTER/SR_OUT_0: Q13.1 (G), R87.1, TP41.1, U11.9 (Q7S)
/ROW_SHIFT_REGISTER/SR_OUT_1: Q14.1 (G), R88.1, TP42.1, U12.9 (Q7S)
GND: C53.2, C54.2, C55.2, C56.2, C57.2, C58.2, C59.2, C60.2, C61.2, C62.2, C63.2, C64.2, Q13.2 (S), Q14.2 (S), R86.2, R87.2, R88.2, U9.8 (GND), U10.8 (GND), U11.8 (GND), U12.8 (GND); also elsewhere on the board
unnamed: Q12.1 (G), Q13.3 (D), Q14.3 (D), R85.2
unnamed: TP39.1, U9.9 (Q7S), U11.14 (DS)
unnamed: TP40.1, U10.9 (Q7S), U12.14 (DS)
ROW00_OFF: U12.7 (Q7); also elsewhere on the board
ROW00_ON: U9.15 (Q0); also elsewhere on the board
ROW01_OFF: U10.15 (Q0); also elsewhere on the board
ROW01_ON: U11.7 (Q7); also elsewhere on the board
ROW02_OFF: U12.6 (Q6); also elsewhere on the board
ROW02_ON: U9.1 (Q1); also elsewhere on the board
ROW03_OFF: U10.1 (Q1); also elsewhere on the board
ROW03_ON: U11.6 (Q6); also elsewhere on the board
ROW04_OFF: U12.5 (Q5); also elsewhere on the board
ROW04_ON: U9.2 (Q2); also elsewhere on the board
ROW05_OFF: U10.2 (Q2); also elsewhere on the board
ROW05_ON: U11.5 (Q5); also elsewhere on the board
ROW06_OFF: U12.4 (Q4); also elsewhere on the board
ROW06_ON: U9.3 (Q3); also elsewhere on the board
ROW07_OFF: U10.3 (Q3); also elsewhere on the board
ROW07_ON: U11.4 (Q4); also elsewhere on the board
ROW08_OFF: U12.3 (Q3); also elsewhere on the board
ROW08_ON: U9.4 (Q4); also elsewhere on the board
ROW09_OFF: U10.4 (Q4); also elsewhere on the board
ROW09_ON: U11.3 (Q3); also elsewhere on the board
ROW10_OFF: U12.2 (Q2); also elsewhere on the board
ROW10_ON: U9.5 (Q5); also elsewhere on the board
ROW11_OFF: U10.5 (Q5); also elsewhere on the board
ROW11_ON: U11.2 (Q2); also elsewhere on the board
ROW12_OFF: U12.1 (Q1); also elsewhere on the board
ROW12_ON: U9.6 (Q6); also elsewhere on the board
ROW13_OFF: U10.6 (Q6); also elsewhere on the board
ROW13_ON: U11.1 (Q1); also elsewhere on the board
ROW14_OFF: U12.15 (Q0); also elsewhere on the board
ROW14_ON: U9.7 (Q7); also elsewhere on the board
ROW15_OFF: U10.7 (Q7); also elsewhere on the board
ROW15_ON: U11.15 (Q0); also elsewhere on the board
ROW_IN: U9.14 (DS), U10.14 (DS); also elsewhere on the board
ROW_ON: U9.10 (MR), U11.10 (MR); also elsewhere on the board
ROW_OUT: Q12.3 (D), R86.1; also elsewhere on the board
ROW_SHCP: U9.12 (STCP), U10.12 (STCP), U11.12 (STCP), U12.12 (STCP); also elsewhere on the board
